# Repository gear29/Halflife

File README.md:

# Halflife
repo for half-life 
PCB
This is a PCB that can can control four 3 pin outputs with data power and ground which will allow the final build to control 2 servos for movement as well as a mini air pump for sticking to walls with suction cups In addition two a camera. It also has a USBC port allowing charge for the battery which is not connected to the board but can be attached as well as being charged from the board. This provides 3.7 v which is reduced to 3.3 then supplied to the esp32 as well as the nrf32 unit with a lower stable voltage. In addition the 3.7 v battery will go into a buck converter to raise it to 5 volts for powering the servos and the air pump. Now that everything is powered the nrf32 unit will give data input to the esp32 allowing it to control the servos.

Assembly 
Take all surface mount components capacitors diodes resistors etc. and sauder then on making sure there in the right orentation and position
Connect the ports and esp32 and nrf32 to board as well as other chips
make sure all connections are stable 

BE aware that the reason that any remaining errors occur is because in the Schematic I connected any unconnected pins to avoid the unconnected pins warning when checking the PCB in the design rules checker to make it easier to navigate to more important waning's but all of these have are not in the layout and the design is not having issues  

BOM
CONN RCP USB2.0 C 6POS SMD RA
IC BATT CNTL LI-ION 1CEL SOT23-5
IC REG LINEAR 3.3V 600MA SOT-25
LED RED DIFFUSED 5MM ROUND T/H
BAG-O-CAPACITORS
IC REG BOOST 5V 2.5A SOT23-5
RF TXRX MOD ISM>1GHZ PCB THTH
RF TXRX MODULE BT PCB TRACE SMD

CAD
This is a gear train that can hold four suction cups and will hold them and flip them in a way such that when it rotates 180 deg if one pair of the suction cups is secured and is the point of rotation then when the it is rotated the other pair will be able to end with contact points on the surface it would stick to.

To assemble simply print all pieces and on the pins add a ball Bering with a gear on top then on the edges do the same thing but with the tube gears and then pish the suction cups into place then route tubing into tubes and out the holes in the side of the tube gear to the center

There is still editing needed as the size of the servo head is still undetermined. as well is final size of the PCB

CONN HEADER VERT 3POS 2.54MM

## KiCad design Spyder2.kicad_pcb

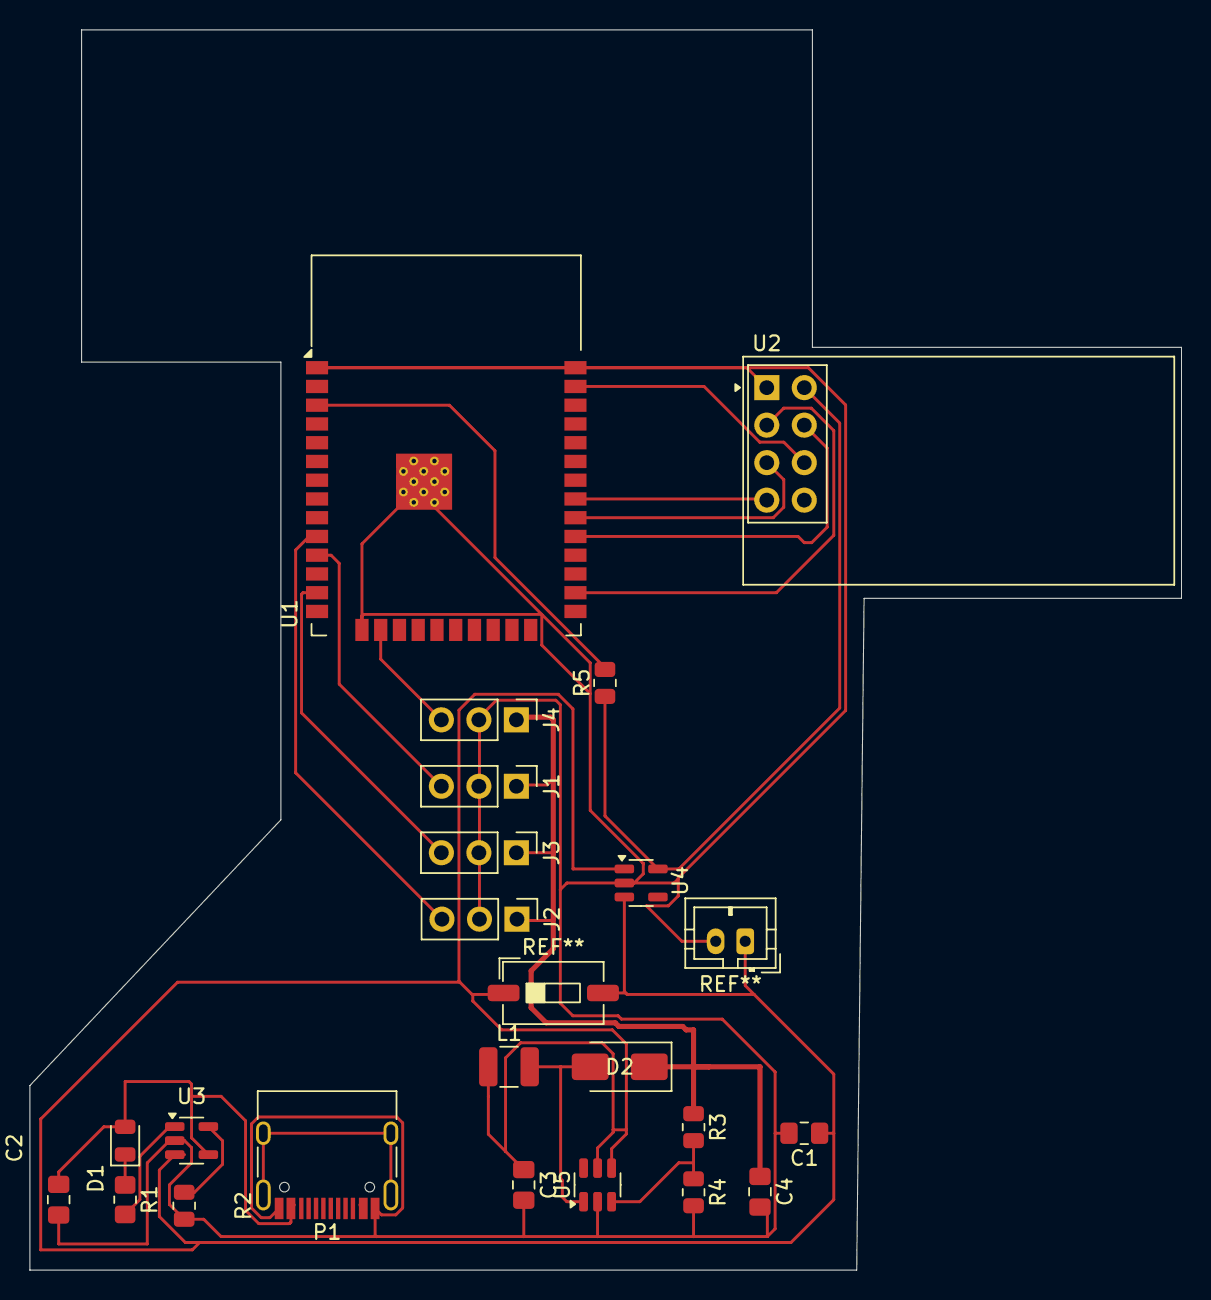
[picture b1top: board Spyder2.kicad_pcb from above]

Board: 2 copper layers, 78.0 x 84.0 mm, 22 parts (0 on the bottom side), 22 nets.

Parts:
C1, C2: 47uf; C_0805_2012Metric_Pad1.18x1.45mm_HandSolder
C3, C4: 22uf; C_0805_2012Metric_Pad1.18x1.45mm_HandSolder
D1: LED; LED_0805_2012Metric
D2: SS34; D_SMA
J1, J2, J3, J4: Conn_01x03; PinHeader_1x03_P2.54mm_Vertical
L1: 4.7uh; L_1210_3225Metric
P1: USB_C_Plug_USB2.0; USB_C_Receptacle_HRO_TYPE-C-31-M-12
R1: 470k; R_0805_2012Metric_Pad1.20x1.40mm_HandSolder
R2: 2K; R_0805_2012Metric
R3: 110k; R_0805_2012Metric
R4: 15k; R_0805_2012Metric
R5: 10k; R_0805_2012Metric
U1: ESP32-WROOM-32E; ESP32-WROOM-32D
U2: NRF24L01_Breakout; nRF24L01_Breakout
U3: MCP73831-2-MC; SOT-23-5
U4: AP2112K-3.3; SOT-23-5
U5: MT3608; SOT-23-6

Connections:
GND: C1.2, C2.2, C3.2, C4.2, J1.2, J2.2, J3.2, J4.2, P1.A1 (GND), P1.A12 (GND), P1.B1 (GND), P1.B12 (GND), R2.2, R4.2, U1.1 (GND), U1.15 (GND), U1.38 (GND), U1.39 (GND), U2.1 (GND), U3.2 (V_{DD}), U4.2 (GND), U5.2 (GND)
unnamed: C4.1, D2.1 (K), J1.1, J2.1, J3.1, J4.1, R3.1
unnamed: D1.1 (K), R1.1
unnamed: D2.2 (A), L1.2, U5.1 (SW)
unnamed: J1.3, U1.11 (IO26)
unnamed: J2.3, U1.10 (IO25)
unnamed: J3.3, U1.13 (IO14)
unnamed: J4.3, U1.16 (IO13)
unnamed: P1.A5 (CC), P1.A6 (D+), P1.A7 (D-), P1.B5 (VCONN)
unnamed: R5.2, U1.3 (EN)
unnamed: U1.26 (IO4), U2.3 (CE)
unnamed: U1.29 (IO5), U2.4 (~CSN)
unnamed: U1.30 (IO18), U2.5 (SCK)
unnamed: U1.31 (IO19), U2.7 (MISO)
unnamed: U1.33 (IO21), U1.36 (IO22)
unnamed: U1.37 (IO23), U2.6 (MOSI)
unnamed: R2.1, U3.5 (STAT)
unnamed: R1.2, U3.1 (V_{DD})
unnamed: R3.2, R4.1, U5.3 (FB)
unnamed: C1.1, C3.1, L1.1, U3.3 (V_{BAT}), U4.1 (VIN), U4.3 (EN), U5.4 (EN), U5.5 (IN)
unnamed: R5.1, U2.2 (VCC), U4.5 (VOUT)
VBUS: C2.1, D1.2 (A), P1.A4 (VBUS), P1.A9 (VBUS), P1.B4 (VBUS), P1.B9 (VBUS), U3.4 (V_{BAT})
